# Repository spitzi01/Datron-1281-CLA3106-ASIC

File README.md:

# Datron-1281-CLA3106-ASIC
Drop-in replacement for Datrons custom ASIC CLA3106 with a 5V CPLD

The Datron 1281 & 1271 multimeters and some Datron products use a custom ASIC for the serial communication inside the instrument. This ASIC in its basic function is nothing more than a bidirectional shift register with error detection. After carefully studying the service manual and making some measurements in my Datron 1281, I was able to replicate the functions of this ASIC. Now a 5V ATMEL CPLD ATF1504 can do the job of this irreplaceable IC. I designed a little PCB which can be installed in a DIP socket. If a CLA3106 breaks, it can be replaced with this PCB. No further modifications are needed.

The CPLD can be ordered preprogrammed from Digikey or programmed by yourself, if you have the necessary equipment. The firmware for the ATF1504 ist in the CLA3106.jed file. The KiCAD project files, Gerber and BOM are all in this repository. I hope with this project some old Datron equipment can be saved.

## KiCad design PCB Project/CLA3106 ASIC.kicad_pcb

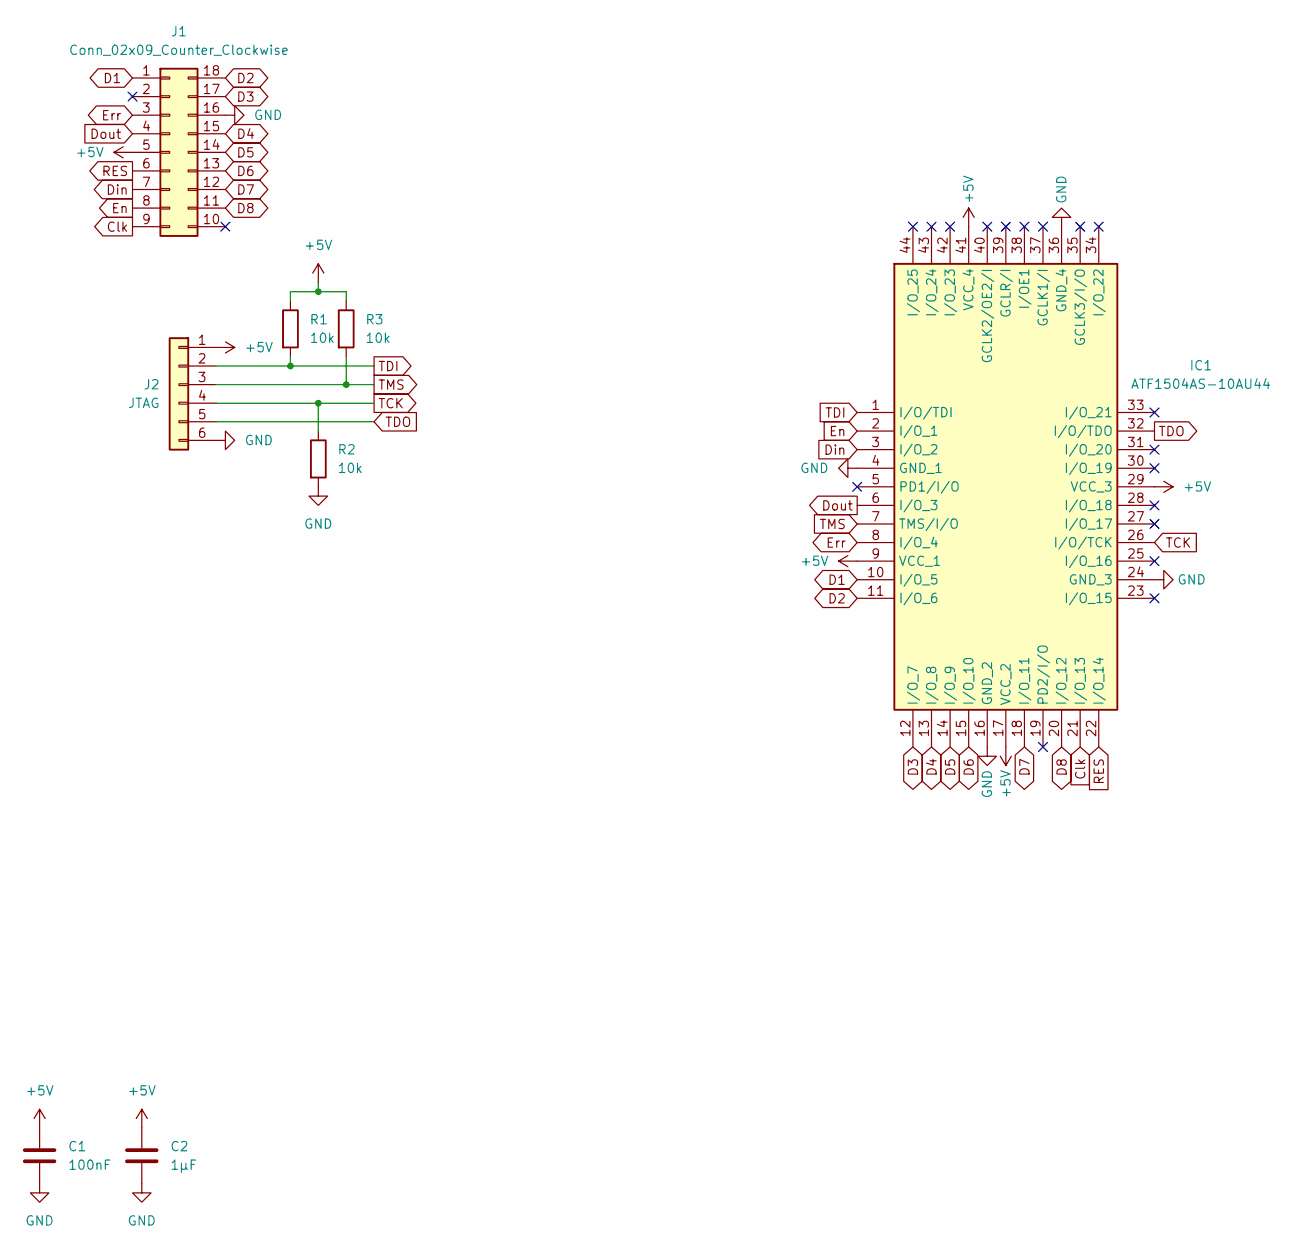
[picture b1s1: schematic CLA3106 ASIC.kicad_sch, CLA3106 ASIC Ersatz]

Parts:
C1: 100nF; C_0805_2012Metric
C2: 1µF; C_0805_2012Metric
IC1: ATF1504AS-10AU44; QFP80P1200X1200X120-44N; Manufacturer_Part_Number ATF1504ASL-25AU44-T; Mouser Part Number 556-AT1504ASL25AU44T
J1: Conn_02x09_Counter_Clockwise; DIP-18_W7.62mm_LongPads
J2: JTAG; PinHeader_1x06_P2.54mm_Vertical
R1, R2, R3: 10k; R_0805_2012Metric

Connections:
+5V: C1.1, C2.1, IC1.9 (VCC_1), IC1.17 (VCC_2), IC1.29 (VCC_3), IC1.41 (VCC_4), J1.5, J2.1, R1.1, R3.1
Clk: IC1.21 (I/O_13), J1.9
D1: IC1.10 (I/O_5), J1.1
D2: IC1.11 (I/O_6), J1.18
D3: IC1.12 (I/O_7), J1.17
D4: IC1.13 (I/O_8), J1.15
D5: IC1.14 (I/O_9), J1.14
D6: IC1.15 (I/O_10), J1.13
D7: IC1.18 (I/O_11), J1.12
D8: IC1.20 (I/O_12), J1.11
Din: IC1.3 (I/O_2), J1.7
Dout: IC1.6 (I/O_3), J1.4
En: IC1.2 (I/O_1), J1.8
Err: IC1.8 (I/O_4), J1.3
GND: C1.2, C2.2, IC1.4 (GND_1), IC1.16 (GND_2), IC1.24 (GND_3), IC1.36 (GND_4), J1.16, J2.6, R2.2
RES: IC1.22 (I/O_14), J1.6
TCK: IC1.26 (I/O/TCK), J2.4, R2.1
TDI: IC1.1 (I/O/TDI), J2.2, R1.2
TDO: IC1.32 (I/O/TDO), J2.5
TMS: IC1.7 (TMS/I/O), J2.3, R3.2

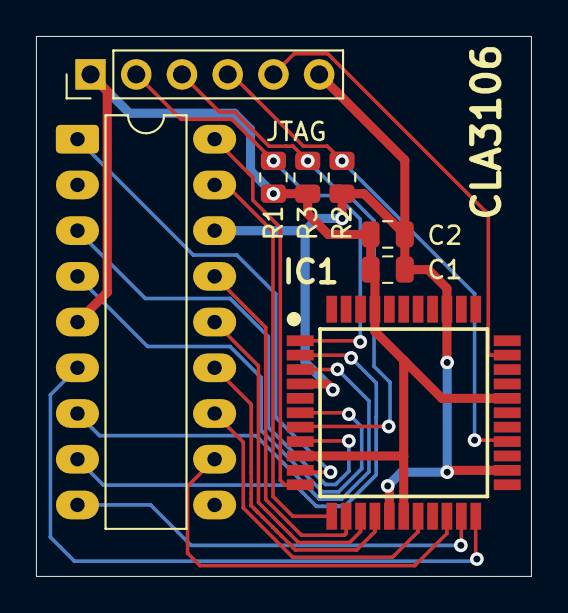
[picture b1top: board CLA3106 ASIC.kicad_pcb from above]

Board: 2 copper layers, 27.5 x 30.0 mm, 8 parts (0 on the bottom side), 20 nets.

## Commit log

2026-05-21 Add files via upload
    Corrected Footprint Library
